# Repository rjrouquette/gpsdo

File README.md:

# GPSDO PTP Master

Redesign of the [Radio Astronomy Master Clock](https://github.com/rjrouquette/radio_astronomy#master-clock) as an IEEE 1588 PTP Master.

## IEEE 1588 PTP Master
- ublox MAX-8Q GPS
- MSP432E401Y
    - integrated EMAC+PHY with PTP support
    - PTP PPS generation for synchronization with GPSDO
- Software discipline of XO frequency and offset
- PPS and 1 kHz reference outputs
- POE powered w/ battery backup
- DHCP client
- NTP server
- PTP server
- SNMP server
- UDP status endpoints

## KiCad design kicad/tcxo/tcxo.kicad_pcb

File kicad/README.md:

# KiCad Projects

This directory contains the KiCad project files for the GPSDO and Ethernet boards.

---
## Ethernet

The IEEE 1588 PTP ethernet board.

Main Files:
- `ethernet.pro`
- `ethernet.sch`
- `ethernet.kicad_pcb`

---
## GPSDO

The GPSDO daughter board.

Main Files:
- `gpsdo.pro`
- `gpsdo.sch`
- `gpsdo.kicad_pcb`

---
### Errata
- 549CAAC000111BBG (25MHz) replaced with 544CAAC000112BBG (10MHz)
    - Lack of inventory for Si549
    - Si544 is reprogrammed by MSP430 to 25MHz on boot

---
### 544CAAC000112BBG
|Product                                    |Si544|
|---                                        |---|
|Description                                |Differential/single-ended; Any frequency (I2C) XO; 0.2-1500 MHz|
|Frequency A                                |10 MHz|
|I2C Address (Hex Format)                   |0x55|
|Output Format and Supply Voltage           |CMOS: 1.8 V, 2.5 V, 3.3 V|
|Temperature Stability / Total Stability    |20 ppm / 50 ppm|
|OE Pin Location and Polarity               |OE Pin1, Active High|
|Frequency Range                            |0.2 - 325 MHz (CMOS available to 250 MHz)|
|Package Option                             |3.2x5 mm|
|Operating Temp Range (°C)                  |-40 to +85|

---
### 549CAAC000111BBG
|Product                                    |Si549|
|---                                        |---|
|Description                                |Differential/single-ended; Any frequency (I2C) XO; 0.2-1500 MHz|
|Frequency A                                |25 MHz|
|I2C Address (Hex Format)                   |0x55|
|Output Format and Supply Voltage           |CMOS: 1.8 V, 2.5 V, 3.3 V|
|Temperature Stability / Total Stability    |20 ppm / 50 ppm|
|OE Pin Location and Polarity               |OE Pin1, Active High|
|Frequency Range                            |0.2 - 325 MHz (CMOS available to 250 MHz)|
|Package Option                             |3.2x5 mm|
|Operating Temp Range (°C)                  |-40 to +85|

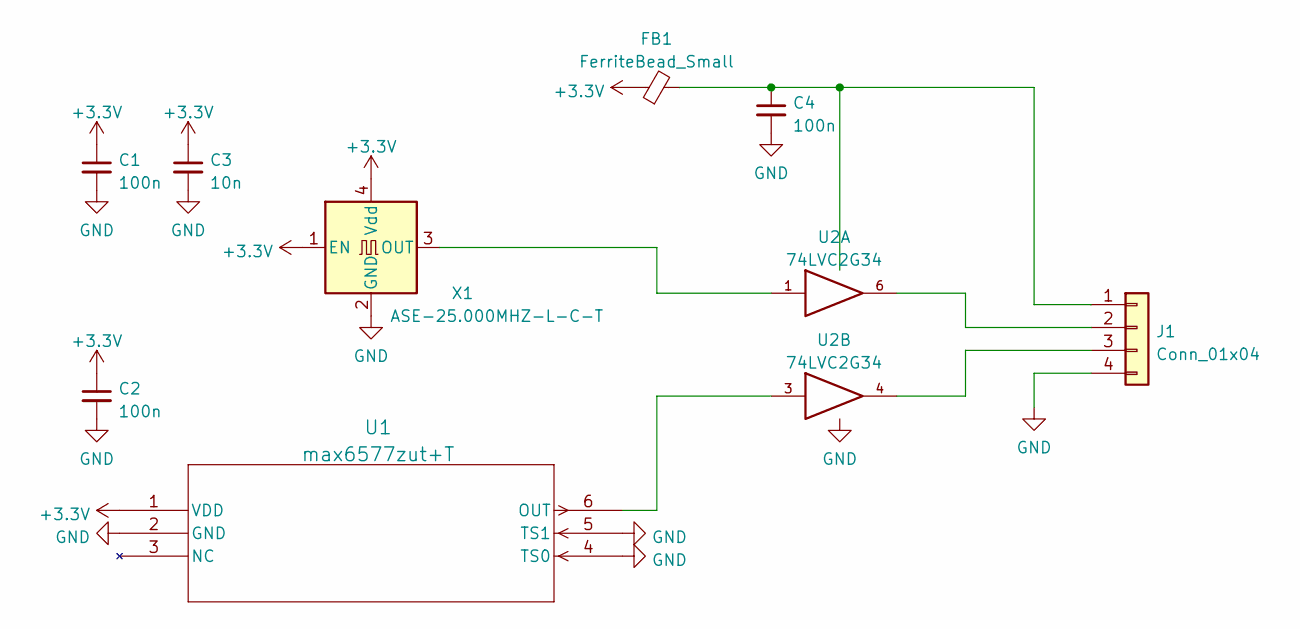
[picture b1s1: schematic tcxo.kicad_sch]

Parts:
C1, C2, C4: 100n; C_0805_2012Metric
C3: 10n; C_0805_2012Metric
FB1: FerriteBead_Small; R_0805_2012Metric
J1: Conn_01x04; PinHeader_1x04_P2.54mm_Vertical
U1: max6577zut+T; SOT-23-6_Handsoldering
U2: 74LVC2G34; SOT-23-6_Handsoldering
X1: ASE-25.000MHZ-L-C-T; Oscillator_SMD_Abracon_ASE-4Pin_3.2x2.5mm

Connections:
+3V3: C1.1, C2.1, C3.1, FB1.1, U1.1 (VDD), X1.1 (EN), X1.4 (Vdd)
GND: C1.2, C2.2, C3.2, C4.2, J1.4, U1.2 (GND), U1.4 (TS0), U1.5 (TS1), U2.2 (GND), X1.2 (GND)
unnamed: J1.2, U2.6
unnamed: J1.3, U2.4
unnamed: U1.6 (OUT), U2.3
unnamed: U2.1, X1.3 (OUT)
VCC: C4.1, FB1.2, J1.1, U2.5 (VCC)

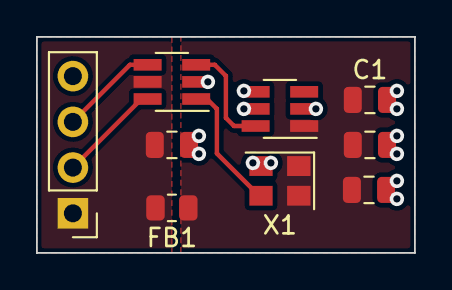
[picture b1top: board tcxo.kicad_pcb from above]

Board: 2 copper layers, 21.0 x 12.0 mm, 9 parts (0 on the bottom side), 7 nets.

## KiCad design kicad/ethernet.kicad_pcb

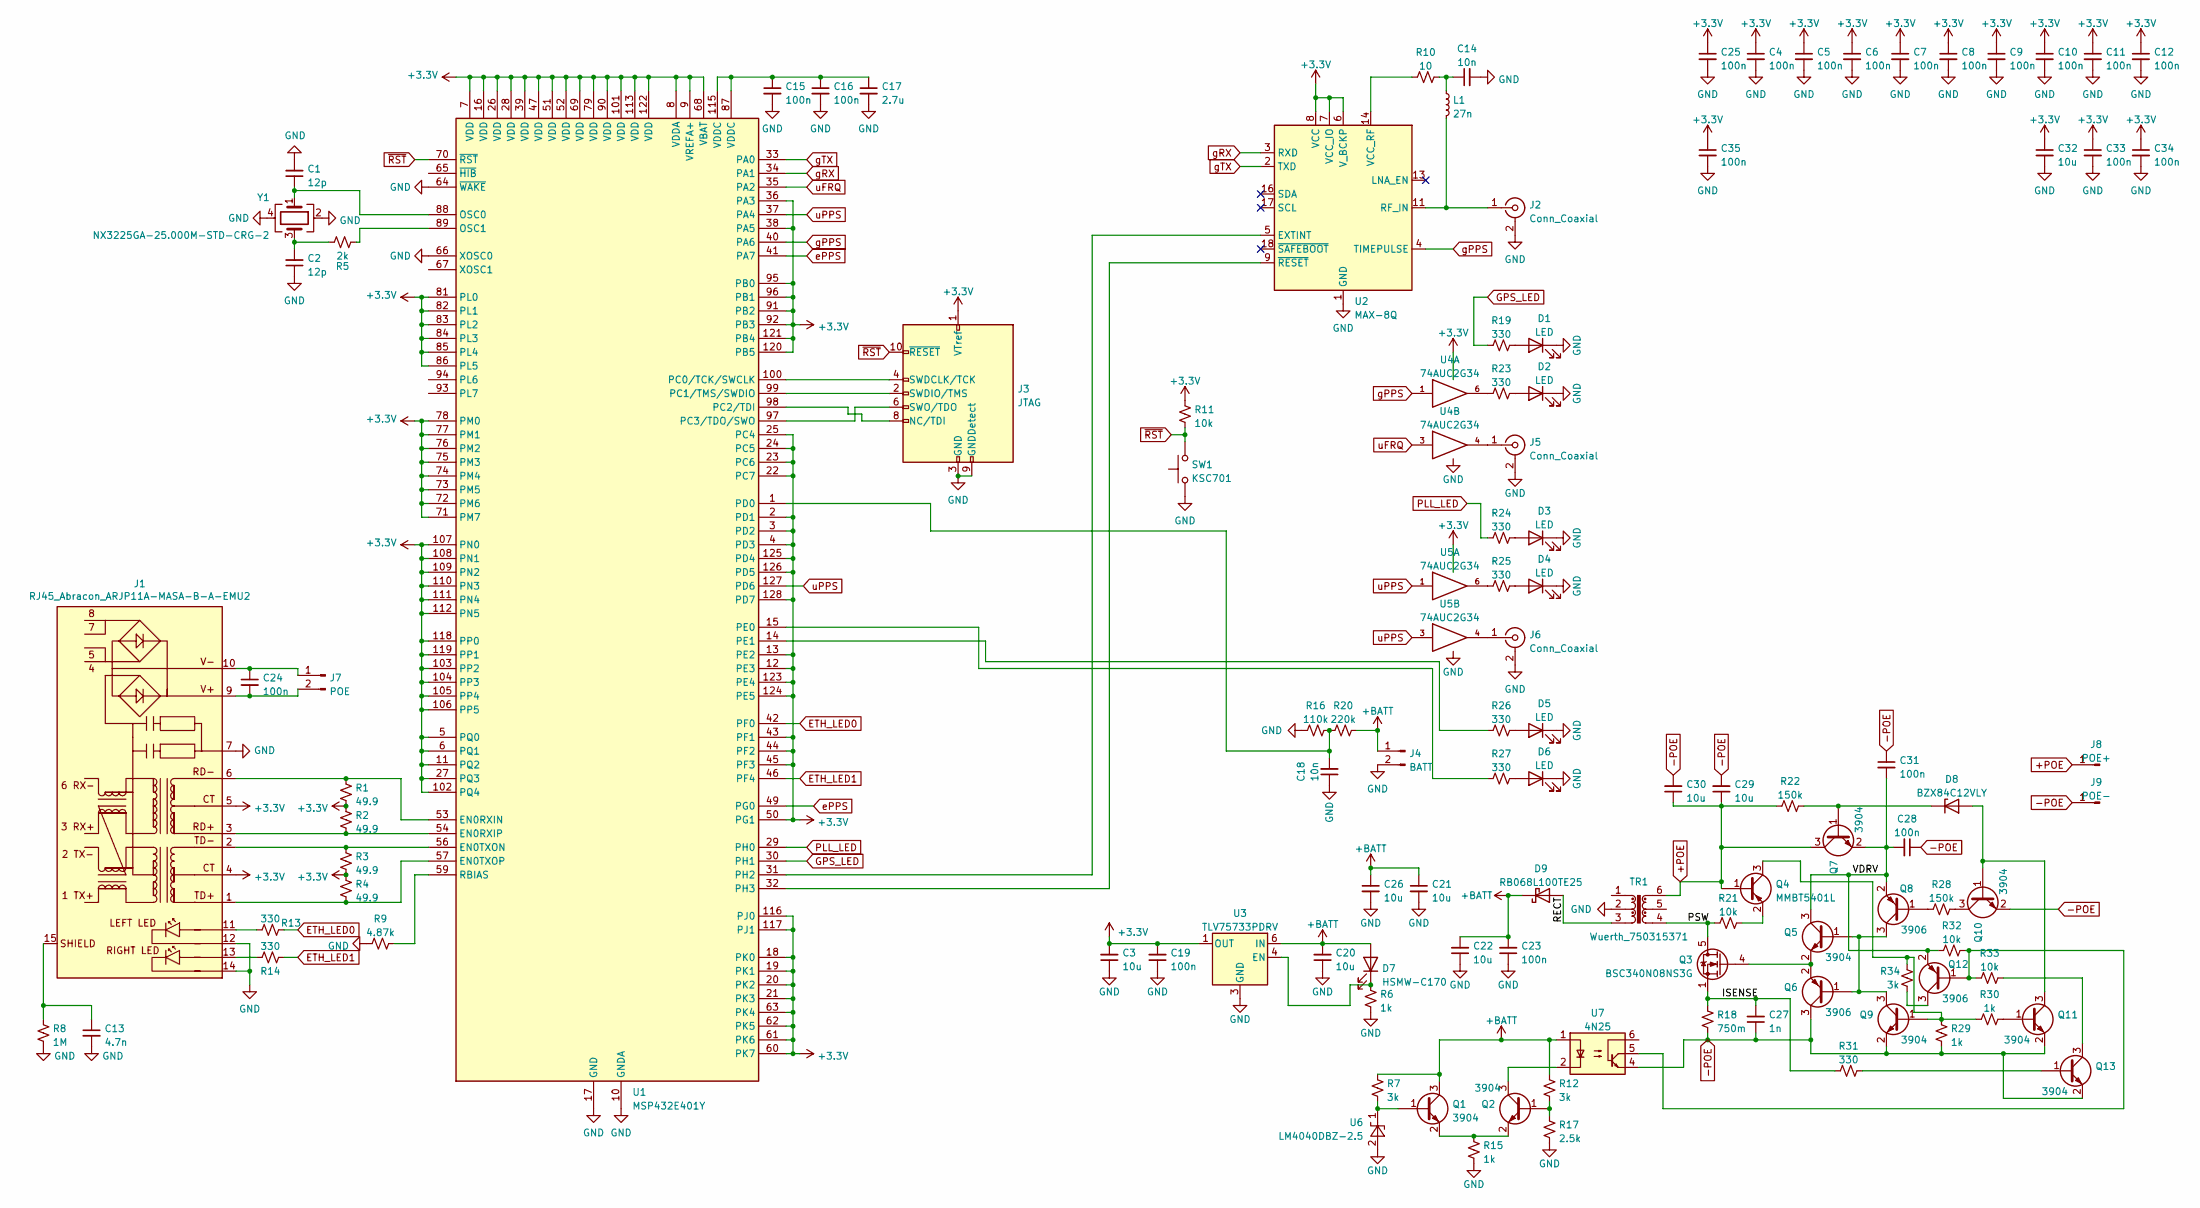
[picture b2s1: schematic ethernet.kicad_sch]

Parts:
C1, C2: 12p; C_0805_2012Metric
C3, C20, C21, C22, C26, C32: 10u; C_0805_2012Metric
C4, C5, C6, C7, C8, C9, C10, C11, C12, C15, C16, C19, C23, C24, C25, C28, C31, C33, C34, C35: 100n; C_0805_2012Metric
C13: 4.7n; C_0805_2012Metric
C14, C18: 10n; C_0805_2012Metric
C17: 2.7u; C_0805_2012Metric
C27: 1n; C_0805_2012Metric
C29, C30: 10u; C_1210_3225Metric
D1, D3, D5: LED; LED_D5.0mm_Horizontal_O3.81mm_Z3.0mm
D2, D4, D6: LED; LED_D5.0mm_Horizontal_O1.27mm_Z3.0mm
D7: HSMW-C170; LED_0805_2012Metric
D8: BZX84C12VLY; D_SOT-23_ANK
D9: RB068L100TE25; D_SMA
J1: RJ45_Abracon_ARJP11A-MASA-B-A-EMU2; RJ45_Abracon_ARJP11A-MA_Horizontal
J2, J5, J6: Conn_Coaxial; SMA_Molex_73251-2120_EdgeMount_Horizontal
J3: JTAG; PinHeader_2x05_P2.54mm_Vertical
J4: BATT; PinHeader_1x02_P2.54mm_Vertical
J7: POE; PinHeader_1x02_P2.54mm_Vertical
J8: POE+; Pin_D0.9mm_L10.0mm_W2.4mm_FlatFork
J9: POE-; Pin_D0.9mm_L10.0mm_W2.4mm_FlatFork
L1: 27n; L_0805_2012Metric
Q1, Q2, Q5, Q7, Q9, Q10, Q11, Q13: 3904; SOT-23
Q3: BSC340N08NS3G; TDSON-8-1
Q4: MMBT5401L; SOT-23
Q6, Q8, Q12: 3906; SOT-23
R1, R2, R3, R4: 49.9; R_0805_2012Metric
R5: 2k; R_0805_2012Metric
R6, R15, R29, R30: 1k; R_0805_2012Metric
R7, R12, R34: 3k; R_0805_2012Metric
R8: 1M; R_0805_2012Metric
R9: 4.87k; R_0805_2012Metric
R10: 10; R_0805_2012Metric
R11, R21, R32, R33: 10k; R_0805_2012Metric
R13, R14, R19, R23, R24, R25, R26, R27, R31: 330; R_0805_2012Metric
R16: 110k; R_0805_2012Metric
R17: 2.5k; R_0805_2012Metric
R18: 750m; R_1206_3216Metric
R20: 220k; R_0805_2012Metric
R22, R28: 150k; R_0805_2012Metric
SW1: KSC701; SW_Push_1P1T_NO_CK_KSC7xxJ
TR1: Wuerth_750315371; Transformer_Wuerth_750315371
U1: MSP432E401Y; LQFP-128_14x14mm_P0.4mm
U2: MAX-8Q; ublox_MAX
U3: TLV75733PDRV; WSON-6-1EP_2x2mm_P0.65mm_EP1x1.6mm
U4, U5: 74AUC2G34; SOT-23-6
U6: LM4040DBZ-2.5; SOT-23
U7: 4N25; SMDIP-6_W9.53mm
Y1: NX3225GA-25.000M-STD-CRG-2; Crystal_SMD_3225-4Pin_3.2x2.5mm

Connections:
+3V3: C3.2, C4.1, C5.1, C6.1, C7.1, C8.1, C9.1, C10.1, C11.1, C12.1, C19.2, C25.1, C32.1, C33.1, C34.1, C35.1, J1.4 (CT), J1.5 (CT), J3.1 (VTref), R1.2, R2.1, R3.2, R4.1, R11.2, U1.2 (PD1), U1.3 (PD2), U1.4 (PD3), U1.5 (PQ0), U1.6 (PQ1), U1.7 (VDD), U1.8 (VDDA), U1.9 (VREFA+), U1.11 (PQ2), U1.12 (PE3), U1.13 (PE2), U1.16 (VDD), U1.18 (PK0), U1.19 (PK1), U1.20 (PK2), U1.21 (PK3), U1.22 (PC7), U1.23 (PC6), U1.24 (PC5), U1.25 (PC4), U1.26 (VDD), U1.27 (PQ3), U1.28 (VDD), U1.36 (PA3), U1.38 (PA5), U1.39 (VDD), U1.43 (PF1), U1.44 (PF2), U1.45 (PF3), U1.47 (VDD), U1.50 (PG1), U1.51 (VDD), U1.52 (VDD), U1.60 (PK7), U1.61 (PK6), U1.62 (PK5), U1.63 (PK4), U1.68 (VBAT), U1.69 (VDD), U1.71 (PM7), U1.72 (PM6), U1.73 (PM5), U1.74 (PM4), U1.75 (PM3), U1.76 (PM2), U1.77 (PM1), U1.78 (PM0), U1.79 (VDD), U1.81 (PL0), U1.82 (PL1), U1.83 (PL2), U1.84 (PL3), U1.85 (PL4), U1.86 (PL5), U1.90 (VDD), U1.91 (PB2), U1.92 (PB3), U1.95 (PB0), U1.96 (PB1), U1.101 (VDD), U1.102 (PQ4), U1.103 (PP2), U1.104 (PP3), U1.105 (PP4), U1.106 (PP5), U1.107 (PN0), U1.108 (PN1), U1.109 (PN2), U1.110 (PN3), U1.111 (PN4), U1.112 (PN5), U1.113 (VDD), U1.116 (PJ0), U1.117 (PJ1), U1.118 (PP0), U1.119 (PP1), U1.120 (PB5), U1.121 (PB4), U1.122 (VDD), U1.123 (PE4), U1.124 (PE5), U1.125 (PD4), U1.126 (PD5), U1.128 (PD7), U2.6 (V_BCKP), U2.7 (VCC_IO), U2.8 (VCC), U3.1 (OUT), U4.5 (VCC), U5.5 (VCC)
+BATT: C20.2, C21.1, C22.2, C23.2, C26.1, D7.2 (A), D9.1 (K), J4.1, Q1.3 (C), R7.2, R12.1, R20.1, U3.6 (IN), U7.1
+POE: C29.1, C30.1, J8.1, Q4.1 (B), Q7.3 (C), R22.2, TR1.6
-POE: C27.1, C28.1, C29.2, C30.2, C31.1, J9.1, Q6.3 (C), Q9.2 (E), Q10.2 (E), Q11.2 (E), Q13.2 (E), R18.1, R29.2, U7.4
/ISENSE: C27.2, Q3.1 (S), Q3.2 (S), Q3.3 (S), R18.2, R31.2
/PSW: Q3.5 (D), R21.2, TR1.4
/RECT: D9.2 (A), TR1.3
/VDRV: C28.2, C31.2, Q5.3 (C), Q7.2 (E), Q8.2 (E), Q12.2 (E), R32.2
ETH_LED0: R13.1, U1.42 (PF0)
ETH_LED1: R14.1, U1.46 (PF4)
GND: C1.2, C2.1, C3.1, C4.2, C5.2, C6.2, C7.2, C8.2, C9.2, C10.2, C11.2, C12.2, C13.2, C14.2, C15.2, C16.2, C17.2, C18.1, C19.1, C20.1, C21.2, C22.1, C23.1, C25.2, C26.2, C32.2, C33.2, C34.2, C35.2, D1.1 (K), D2.1 (K), D3.1 (K), D4.1 (K), D5.1 (K), D6.1 (K), J1.7, J1.12 (LLED-), J1.14 (RLED-), J2.2 (Ext), J3.3 (GND), J3.5 (GND), J3.9 (GNDDetect), J4.2, J5.2 (Ext), J6.2 (Ext), R6.1, R8.1, R9.1, R15.1, R16.2, R17.1, SW1.1, TR1.2, U1.10 (GNDA), U1.17 (GND), U1.48 (GND), U1.55 (GND), U1.58 (GND), U1.64 (~WAKE), U1.66 (XOSC0), U1.80 (GND), U1.114 (GND), U2.1 (GND), U2.10 (GND), U2.12 (GND), U3.3 (GND), U3.7 (GND), U4.2 (GND), U5.2 (GND), U6.2 (A), Y1.2, Y1.4
GPS_LED: R19.2, U1.30 (PH1)
unnamed: C1.1, U1.88 (OSC0), Y1.1
unnamed: C2.2, R5.2, Y1.3
unnamed: C13.1, J1.15 (SHIELD), R8.2
unnamed: C14.1, L1.1, R10.2
unnamed: C15.1, C16.1, C17.1, U1.87 (VDDC), U1.115 (VDDC)
unnamed: C18.2, R16.1, R20.2, U1.1 (PD0)
unnamed: C24.1, J1.10 (V-), J7.1
unnamed: C24.2, J1.9 (V+), J7.2
unnamed: D1.2 (A), R19.1
unnamed: D2.2 (A), R23.1
unnamed: D3.2 (A), R24.1
unnamed: D4.2 (A), R25.1
unnamed: D5.2 (A), R26.1
unnamed: D6.2 (A), R27.1
unnamed: D7.1 (K), R6.2, U3.4 (EN)
unnamed: D8.1 (K), Q7.1 (B), R22.1
unnamed: D8.2 (A), Q10.1 (B), Q11.3 (C)
unnamed: J1.1 (TD+), R4.2, U1.57 (EN0TXOP)
unnamed: J1.2 (TD-), R3.1, U1.56 (EN0TXON)
unnamed: J1.3 (RD+), R2.2, U1.54 (EN0RXIP)
unnamed: J1.6 (RD-), R1.1, U1.53 (EN0RXIN)
unnamed: J1.11 (LLED+), R13.2
unnamed: J1.13 (RLED+), R14.2
unnamed: J2.1 (In), L1.2, U2.11 (RF_IN)
unnamed: J3.2 (SWDIO/TMS), U1.99 (PC1/TMS/SWDIO)
unnamed: J3.4 (SWDCLK/TCK), U1.100 (PC0/TCK/SWCLK)
unnamed: J3.6 (SWO/TDO), U1.97 (PC3/TDO/SWO)
unnamed: J3.8 (NC/TDI), U1.98 (PC2/TDI)
unnamed: J5.1 (In), U4.4
unnamed: J6.1 (In), U5.4
unnamed: Q1.1 (B), R7.1, U6.1 (K)
unnamed: Q1.2 (E), Q2.2 (E), R15.2
unnamed: Q2.1 (B), R12.2, R17.2
unnamed: Q2.3 (C), U7.2
unnamed: Q3.4 (G), Q5.2 (E), Q6.2 (E)
unnamed: Q4.2 (E), R21.1
unnamed: Q4.3 (C), Q9.1 (B), R29.1, R30.1, R34.1
unnamed: Q5.1 (B), Q6.1 (B), Q8.3 (C), Q9.3 (C)
unnamed: Q8.1 (B), R28.2
unnamed: Q10.3 (C), R28.1
unnamed: Q11.1 (B), R30.2
unnamed: Q12.1 (B), R32.1, R33.2, U7.5
unnamed: Q12.3 (C), R34.2
unnamed: Q13.1 (B), R31.1
unnamed: Q13.3 (C), R33.1
unnamed: R5.1, U1.89 (OSC1)
unnamed: R9.2, U1.59 (RBIAS)
unnamed: R10.1, U2.14 (VCC_RF)
unnamed: R23.2, U4.6
unnamed: R25.2, U5.6
unnamed: R26.2, U1.14 (PE1)
unnamed: R27.2, U1.15 (PE0)
unnamed: U1.31 (PH2), U2.5 (EXTINT)
unnamed: U1.32 (PH3), U2.9 (~RESET)
PLL_LED: R24.2, U1.29 (PH0)
ePPS: U1.41 (PA7), U1.49 (PG0)
gPPS: U1.40 (PA6), U2.4 (TIMEPULSE), U4.1
gRX: U1.34 (PA1), U2.3 (RXD)
gTX: U1.33 (PA0), U2.2 (TXD)
uFRQ: U1.35 (PA2), U4.3
uPPS: U1.37 (PA4), U1.127 (PD6), U5.1, U5.3
~RST: J3.10 (~RESET), R11.1, SW1.2, U1.70 (~RST)

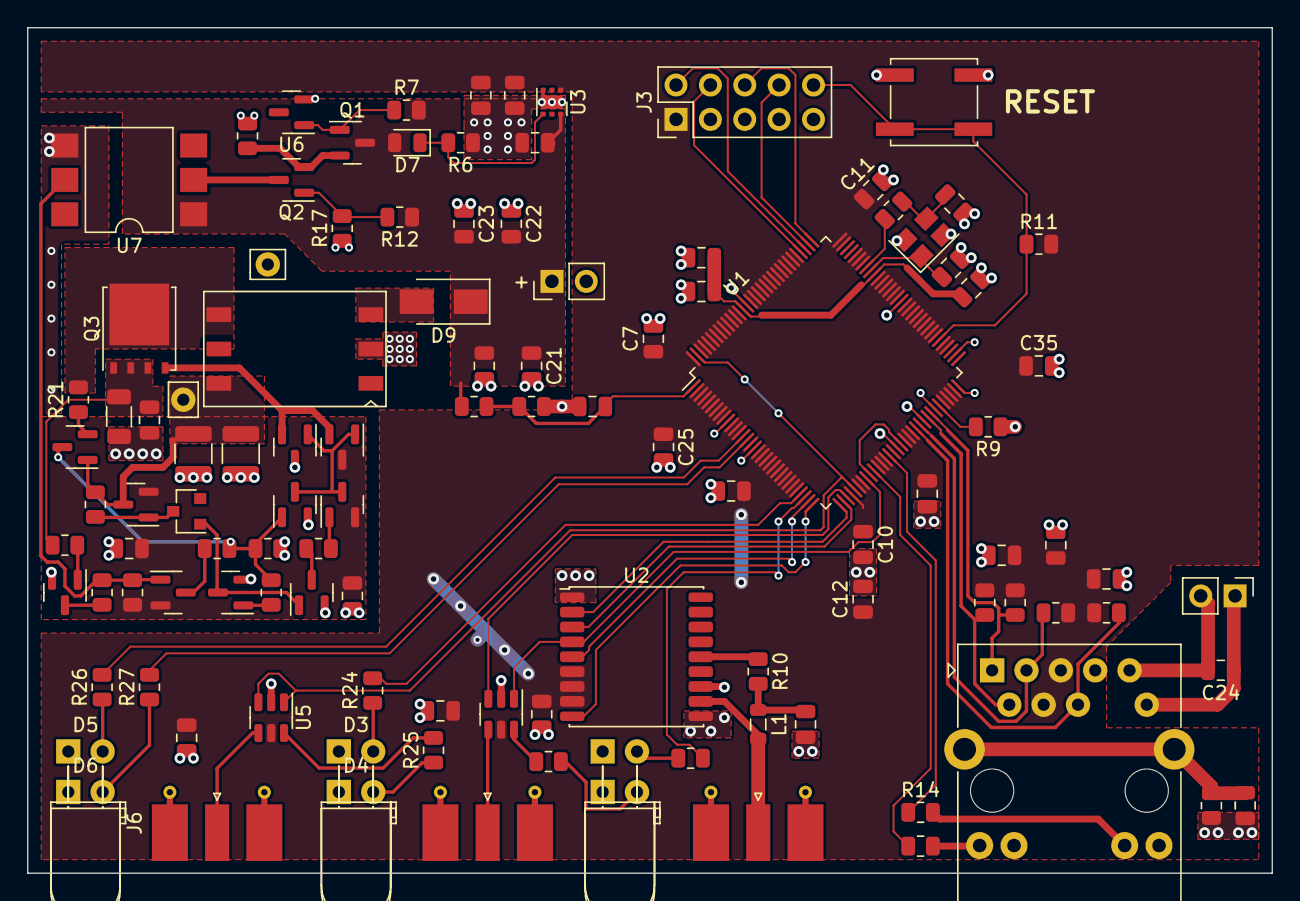
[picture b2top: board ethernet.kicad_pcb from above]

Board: 2 copper layers, 92.0 x 62.5 mm, 111 parts (0 on the bottom side), 74 nets.

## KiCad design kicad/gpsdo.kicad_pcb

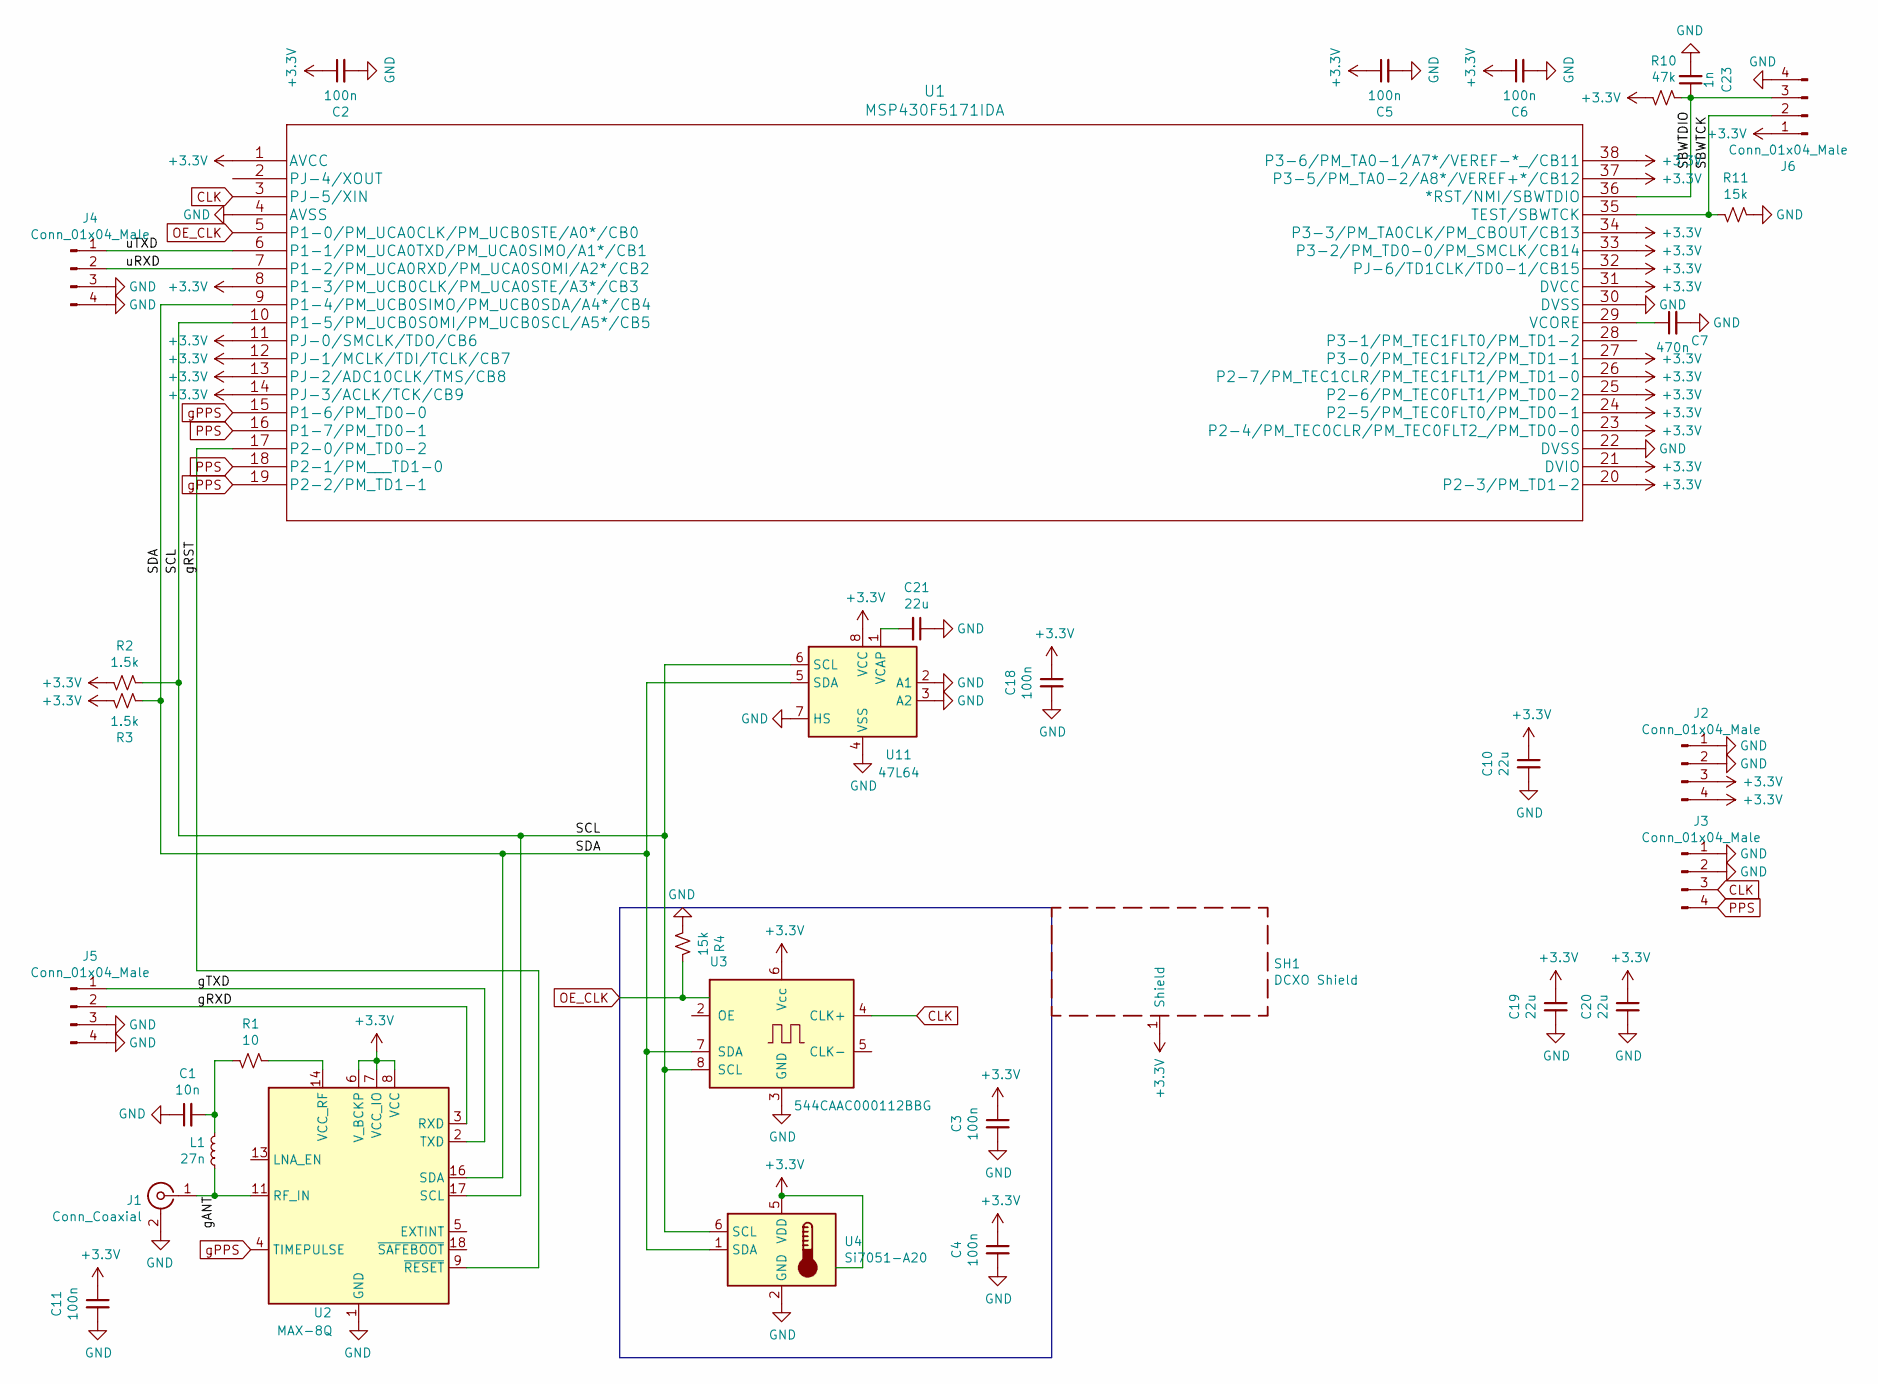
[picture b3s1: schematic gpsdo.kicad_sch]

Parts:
C1: 10n; R_0603_1608Metric
C2, C3, C4, C5, C6, C11, C18: 100n; R_0603_1608Metric
C7: 470n; C_0805_2012Metric
C10, C19, C20, C21: 22u; C_0805_2012Metric
C23: 1n; R_0603_1608Metric
J1: Conn_Coaxial; SMA_Molex_73251-1153_EdgeMount_Horizontal
J2, J3, J4, J5, J6: Conn_01x04_Male; PinHeader_1x04_P2.54mm_Vertical
L1: 27n; R_0603_1608Metric
R1: 10; R_0603_1608Metric
R2, R3: 1.5k; R_0603_1608Metric
R4, R11: 15k; R_0603_1608Metric
R10: 47k; R_0603_1608Metric
SH1: DCXO Shield; Laird_Technologies_BMI-S-102_16.50x16.50mm
U1: MSP430F5171IDA; TSSOP-38_4.4x9.7mm_P0.5mm
U2: MAX-8Q; ublox_MAX
U3: 544CAAC000112BBG; Oscillator_SMD_SI570_SI571_Standard
U4: Si7051-A20; DFN-6-1EP_3x3mm_P1mm_EP1.5x2.4mm
U11: 47L64; SOIC-8_3.9x4.9mm_P1.27mm

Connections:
+3V3: C2.1, C3.1, C4.1, C5.1, C6.1, C10.1, C11.1, C18.1, C19.1, C20.1, J2.3, J2.4, J6.1, R2.1, R3.2, R10.1, SH1.1, U1.1 (AVCC), U1.8 (P1-3/PM_UCB0CLK/PM_UCA0STE/A3*/CB3), U1.11 (PJ-0/SMCLK/TDO/CB6), U1.12 (PJ-1/MCLK/TDI/TCLK/CB7), U1.13 (PJ-2/ADC10CLK/TMS/CB8), U1.14 (PJ-3/ACLK/TCK/CB9), U1.20 (P2-3/PM_TD1-2), U1.21 (DVIO), U1.23 (P2-4/PM_TEC0CLR/PM_TEC0FLT2_/PM_TD0-0), U1.24 (P2-5/PM_TEC0FLT0/PM_TD0-1), U1.25 (P2-6/PM_TEC0FLT1/PM_TD0-2), U1.26 (P2-7/PM_TEC1CLR/PM_TEC1FLT1/PM_TD1-0), U1.27 (P3-0/PM_TEC1FLT2/PM_TD1-1), U1.31 (DVCC), U1.32 (PJ-6/TD1CLK/TD0-1/CB15), U1.33 (P3-2/PM_TD0-0/PM_SMCLK/CB14), U1.34 (P3-3/PM_TA0CLK/PM_CBOUT/CB13), U1.37 (P3-5/PM_TA0-2/A8*/VEREF+*/CB12), U1.38 (P3-6/PM_TA0-1/A7*/VEREF-*_/CB11), U2.6 (V_BCKP), U2.7 (VCC_IO), U2.8 (VCC), U3.6 (Vcc), U4.4 (NC), U4.5 (VDD), U11.8 (VCC)
/SBWTCK: J6.2, R11.1, U1.35 (TEST/SBWTCK)
/SBWTDIO: C23.1, J6.3, R10.2, U1.36 (*RST/NMI/SBWTDIO)
/SCL: R2.2, U1.10 (P1-5/PM_UCB0SOMI/PM_UCB0SCL/A5*/CB5), U2.17 (SCL), U3.8 (SCL), U4.6 (SCL), U11.6 (SCL)
/SDA: R3.1, U1.9 (P1-4/PM_UCB0SIMO/PM_UCB0SDA/A4*/CB4), U2.16 (SDA), U3.7 (SDA), U4.1 (SDA), U11.5 (SDA)
/gANT: J1.1 (In), L1.2, U2.11 (RF_IN)
/gRST: U1.17 (P2-0/PM_TD0-2), U2.9 (~RESET)
/gRXD: J5.2, U2.3 (RXD)
/gTXD: J5.1, U2.2 (TXD)
/uRXD: J4.2, U1.7 (P1-2/PM_UCA0RXD/PM_UCA0SOMI/A2*/CB2)
/uTXD: J4.1, U1.6 (P1-1/PM_UCA0TXD/PM_UCA0SIMO/A1*/CB1)
CLK: J3.3, U1.3 (PJ-5/XIN), U3.4 (CLK+)
GND: C1.1, C2.2, C3.2, C4.2, C5.2, C6.2, C7.2, C10.2, C11.2, C18.2, C19.2, C20.2, C21.1, C23.2, J1.2 (Ext), J2.1, J2.2, J3.1, J3.2, J4.3, J4.4, J5.3, J5.4, J6.4, R4.1, R11.2, U1.4 (AVSS), U1.22 (DVSS), U1.30 (DVSS), U2.1 (GND), U2.10 (GND), U2.12 (GND), U3.3 (GND), U4.2 (GND), U11.2 (A1), U11.3 (A2), U11.4 (VSS), U11.7 (HS)
unnamed: C1.2, L1.1, R1.1
unnamed: C7.1, U1.29 (VCORE)
unnamed: C21.2, U11.1 (VCAP)
unnamed: R1.2, U2.14 (VCC_RF)
OE_CLK: R4.2, U1.5 (P1-0/PM_UCA0CLK/PM_UCB0STE/A0*/CB0), U3.1 (NC)
PPS: J3.4, U1.16 (P1-7/PM_TD0-1), U1.18 (P2-1/PM___TD1-0)
gPPS: U1.15 (P1-6/PM_TD0-0), U1.19 (P2-2/PM_TD1-1), U2.4 (TIMEPULSE)

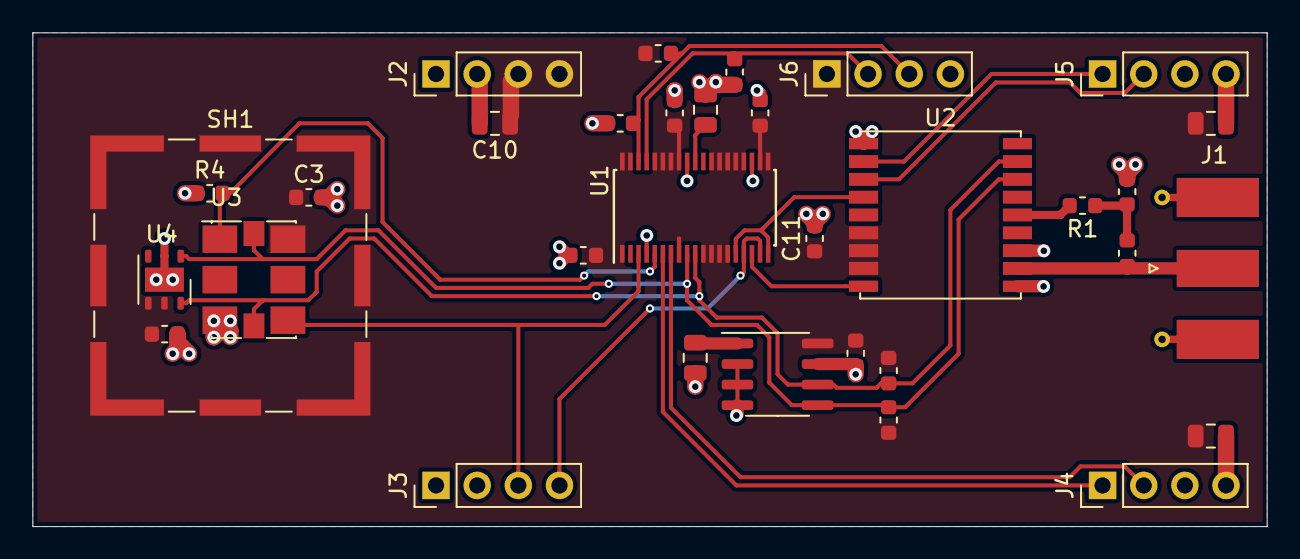
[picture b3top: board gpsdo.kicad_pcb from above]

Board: 2 copper layers, 76.2 x 30.5 mm, 33 parts (0 on the bottom side), 20 nets.

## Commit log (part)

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2023-04-27 restructure clock system to support independent frequency and offset discipline
2023-04-28 restructure clock synchronization
2023-04-28 rename CLK_TRIM to CLK_COMP
2023-04-28 add lease expiration to ethernet status
2023-04-29 code cleanup
2023-04-29 debugging automatic peer removal
2023-04-29 stability improvements
2023-04-30 implement chronyc ntpdata support
2023-04-30 improve chronyc ntpdata support
2023-04-30 integrating temperature compensation into new ntp framework
2023-04-30 implement PLL tracking stats
2023-04-30 implementing ntp source selection
2023-05-01 implement automatic reset of GPS if PPS has stalled
2023-05-01 fix GPS epoch alignment issue
2023-05-01 extra hardening
2023-05-01 stabilize startup timing of ethernet clock synchronization
2023-05-01 fix precision issue with NTP server startup
2023-05-01 clamp offset PLL slew rate
2023-05-01 fix PLL stability
2023-05-01 cleanup polling fuzz
2023-05-02 implement basic source selection
2023-05-02 re-enable gpsdo snmp data
2023-05-02 initialize TAI offset
2023-05-02 fix gps status
2023-05-02 remove debug lines from peer.c
2023-05-02 reduce timekeeping overhead
2023-05-02 fix drift caused by integer truncation in pll
2023-05-02 faster gps startup
2023-05-03 cleanup tcmp.c
2023-05-03 prune high stratum servers
2023-05-03 add MSP432E401Y docs to README.md
2023-05-03 implementing SOM filtering for temperature compensation
2023-05-03 cleanup README.md
2023-05-03 cleanup SNMP sensor code
2023-05-03 add SOM test spreadsheet
2023-05-04 debugging SNMP
2023-05-04 fix SNMP bug
2023-05-04 implement missing OIDs for physical sensors to comply with RFC.
2023-05-04 cleanup snmp sensor values
2023-05-04 simplify SNMP sensor code to use static registry table
2023-05-04 add simple cpp file to test som regression
2023-05-04 fix bug in regression test
2023-05-04 implement dynamic learning rate for som to minimize initial learning period
2023-05-04 testing som regression
2023-05-04 fix float to ascii conversion
2023-05-05 implement cubic regression in temperature compensation
2023-05-05 fix scale for GPS frequency accuracy
2023-05-05 fix formatting for GPS status
2023-05-05 testing som
2023-05-05 testing hysteresis compensation
2023-05-05 add RMSE gating to coefficient regression
2023-05-05 address som boostrap instability
2023-05-06 remove attempt at hysteresis compensation
2023-05-06 load saved temperature compensation immediately at power-on
2023-05-06 evaluating som preformance
2023-05-06 fix minimum clk update rate
2023-05-06 fix temperature smoothing
2023-05-06 fix clock names in status.c
2023-05-06 updating schematic
2023-05-07 add some ptp example code (from the ti.com forum)
2023-05-07 implementing preliminary PTP master
2023-05-08 update schematic
2023-05-08 enable reception of multicast messages
2023-05-08 simulating poe
2023-05-09 poe supply design
2023-05-09 poe power supply design
2023-05-11 fix ntp detection of pps failure
2023-05-11 test changes to compensation regression
2023-05-12 reduce som size to 16 nodes
2023-05-13 improve som behavior
2023-05-14 implement frequency output
2023-05-15 implement PPS output
2023-05-15 fix GPS status flapping
2023-05-15 trim input delay
2023-05-15 improve ntp source selection
2023-05-15 fix comment
2023-05-15 fix linker error
2023-05-15 cleanup NTP GPS code
2023-05-15 fix int64_t to float conversion
2023-05-15 add more comments
2023-05-15 add ISR stub to handle spurious events
2023-05-15 reduce frequency output to 1.0 kHz
2023-05-16 implement centralized task scheduler
2023-05-16 reduce GPS UART overhead
2023-05-16 adjust interrupt priority
2023-05-16 return frequency output to 1 kHz
2023-05-16 migrate NTP tasks to centralized scheduler
2023-05-16 reduce CLK_PPS() overhead
2023-05-16 trim scheduler task slots
2023-05-16 improving scheduler efficiency
2023-05-16 improve scheduling efficiency
2023-05-16 make TX callback thread dynamic
2023-05-16 reduce network polling rate
2023-05-16 cleanup GPS scheduling
2023-05-16 debugging TX callback scheduling
2023-05-16 fix dynamic threads
2023-05-17 increase temperature smoothing
2023-05-17 increase UART polling rate
2023-05-17 relax scheduling
2023-05-17 improve scheduler efficiency
2023-05-18 use UART RX interrupt
2023-05-18 use UART TX interrupt
2023-05-18 additional comments
2023-05-18 remove drift integration term (stability improvement)
2023-05-18 fix recently introduced bug
2023-05-18 faster polling for local timeservers
2023-05-18 board layout progress
2023-05-19 reduce ntp memory footprint
2023-05-19 code cleanup (remove unnecessary usage of volatile keyword)
2023-05-19 implement extended range for runOnce()
2023-05-19 fix runCancel() to handle extended run-once tasks
2023-05-20 fix bug in extended run-once behavior
2023-05-20 cleanup NTP scheduling
2023-05-20 enable reception of ARP broadcast packets; switch to PTPoE
2023-05-20 switch to PTPoE
2023-05-20 reduce UART interrupt priority
2023-05-20 implement PTP responses
2023-05-20 use software packet filtering
2023-05-21 increase PTP sync rate
2023-05-23 cleanup scheduler status
2023-05-23 cleanup PTP code
2023-05-23 verify som behavior
2023-05-23 remove old code
2023-05-23 board layout update
2023-05-24 finishing board layout
2023-05-24 fix loss-of-source indication in NTP and PTP
2023-05-25 improved task scheduling
2023-05-26 cleanup task scheduling code
2023-05-26 fix sign of offset rms and stddev on initial sample
2023-05-26 improve stability of temperature compensation
2023-05-26 tweak temperature measurement
2023-05-27 reduce scheduler memory footprint
2023-05-28 denoise temperature measurement
2023-06-07 tighten possible edge case in runParse() timing
2023-06-07 simplify scheduler
2023-06-08 improve GPS parser fault tolerance
2023-06-08 add register map for fault status
2023-06-11 cleanup task scheduler code
2023-06-11 reduce pll stats alpha
2023-06-11 increase time constant for temperature filtering
2023-06-13 soften offset PLL
2023-06-13 tighten offset PLL
2023-07-21 fix segfault on boot
2023-07-21 remove ISR decoration (per TI documentation and examples)
2023-08-06 change scheduler duration argument type to uint32_t
2023-08-10 debugging lockups
2023-09-15 cleanup usage of GPTM ICR register
2023-09-15 remove input delay trimming from ISRs
2023-09-15 cleanup task scheduler
2023-09-18 remove hard-edge in sample exclusion
2023-09-18 evaluate new compensation regression method
2023-09-18 new regression method
2023-09-19 reduce som learning rate
2023-09-19 further compartmentalization of regression
2023-09-19 fix memory fault
2024-03-21 fix leap year math
2024-03-26 increment eeprom version
2024-03-28 migrating to C++
2024-04-05 migrate task scheduler to c++
2024-04-05 cleanup CMakeLists.txt
2024-04-05 set GPS dynamic model to stationary
2024-04-06 fix gps reset
2024-04-07 add missing field initializers in ntp::Source constructor
2024-04-07 add debug.sh
2024-04-07 improve scheduling
2024-04-11 change core speed to 125 MHz
2024-04-11 add ram/flash used to system status
2024-04-16 faster sampling for temperature compensation
2024-04-16 add separate TCXO board
2024-04-17 cleanup clock framework
2024-04-19 implementing new temperature sensor support
2024-04-23 debugging lockup
2024-04-30 new temperature sensor
2024-04-30 external oscillator
2024-05-06 ethernet driver improvements
2024-05-06 increase minimum interval between automatic GPS resets
2024-05-06 cleaning up network api
2024-05-09 increase temperature filter time constant to two seconds
2024-05-11 cleaner initialization of temperature sensor
2024-05-11 fix NTP server bug
2024-05-11 debugging NTP synchronization
2024-05-13 simplify NTP statistics
2024-05-13 port RGR_FindBestRegression from chrony project
2024-05-16 implement linear regression filtering
2024-05-16 relax pll tracking
2024-05-17 debugging temperature glitches
2024-05-18 fix temperature sensor startup
2024-05-19 reduce weight of temperature sample outliers
2024-05-24 increase temperature capture ring buffer size
2024-05-24 enable ethernet overflow interrupt
2024-05-31 debugging ethernet rx overflow
2024-06-05 24-bit capture resolution
2024-06-05 add configured clock frequency to system status response
2024-06-05 new network api
2024-06-07 testing new temperature smoothing method
2024-06-08 improve smoothness of temperature measurement
2024-06-08 report actual compensation trim value
2024-06-08 fix bug in temperature correction
2024-06-09 reduce temperature measurement overhead
2024-06-10 extend precision of som accumulation
